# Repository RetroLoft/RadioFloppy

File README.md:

# RadioFloppy

WiFi-floppy-emulator voor de Atari ST op basis van een ESP32-S3 (Otronic DevKitC-clone,
16 MB flash, 8 MB PSRAM) op de RadioFloppy-PCB revisie 2 (`hardware/v1.1`).
Framework: ESP-IDF v5.5.5 (C).

## Hardwaretests

`main/main.c` kiest welke test draait (roep de gewenste functie uit `main/tests.h` aan):

| Test | Bestand | Wat |
| ---- | ------- | --- |
| `floppy_emu_run()` (actief) | `main/floppy_app.c`, `sd_card.c`, `disk_copy.c`, `drive_emu.c`, `flux_stream.c`, `mfm_track.c`, `disk_image.c` | Floppy-emulatie als drive B: (`EMU_SELECT_LINE`). De image (.ST of HFE) komt van de SD-kaart (J5), bij opstarten zonder kaart uit de kopie van de laatste disk op de externe SPI-flash U2 (zie `docs/FLASH_LAYOUT.md`), of uit een tijdelijke PSRAM-upload (.ST). Alle 168 sporen worden bij het opstarten naar MFM gecodeerd in PSRAM (FlashFloppy-layout voor .ST: geen IAM, GAP4a 80, GAP2 22, GAP3 84). RMT+DMA speelt de fluxstroom op GPIO41 (0,8 us pulsen, 10 MHz), een tweede RMT-kanaal de INDEX-puls op GPIO1 (3 ms per 200 ms, synchroon gestart). WPROT volgt de schrijfbeveiliging van de disk; geschreven sectoren worden opgeslagen (zie `docs/API.md` → *Writing*). |
| (oud) `legacy/input_monitor.c` | niet gebouwd | Selectiebewuste monitor met TRACK0 uit de vorige fase, ter referentie. |
| `loopback_test_run()` | `main/loopback_test.c` | Zoekt continu welke Shugart-uitgang (ULN2003A) via een jumper op J1 met welke ingang (SN74LVC245A) verbonden is. |

**Loopbacktest:** de Shugart-lijnen hebben op de PCB geen pull-ups (behalve DS0/DS1). Plaats op de jumper een
pull-up van 4,7–10 kΩ naar +3V3 (bijv. J3 pin 3, displayconnector), anders komt de lijn na het
vrijgeven van de uitgang niet betrouwbaar HIGH en wordt er niets gemeld.

**Webinterface:** `http://<ip>/` — Current Floppy, tijdelijk laden (PSRAM), *New disk* en het SD-kaartblok (mappen, uploaden, inserten, verwijderen) vanuit de browser
(`web/index.html`, in de firmware ingebouwd); tandwiel rechtsboven = instellingen (hostnaam,
firmware). **Knoppen:** links = vorige disk, rechts = volgende, binnen de map van de laatst gekozen disk (geen rondgang); beide 3 s = hostnaam en IP op het
display; beide 10 s = WiFi-setupmodus.

**WiFi-setupmodus:** zonder ingesteld netwerk (of na 10 s beide knoppen) opent RadioFloppy een
eigen WiFi-netwerk met één setup-pagina (netwerk, beveiliging, wachtwoord). De diskemulatie is dan
uit; het display toont netwerknaam, sleutel en adres. Zie `docs/API.md` → *WiFi setup mode*.

**WiFi en HTTP API:** `docs/API.md` — images uploaden (tijdelijk naar PSRAM of als bestand op de SD-kaart),
images van de SD-kaart inserten, mappen en bestanden beheren via `/api/v1/`. Hostnaam en WiFi-netwerk staan op de
externe flash (instellingen, setupmodus); `idf.py menuconfig` → *RadioFloppy* geeft alleen de
standaardwaarden en het optionele API-token, en staat alleen in `sdkconfig` (git-ignored). Standaard is de
API open op het thuisnetwerk. Tests:
`tests/host/run.sh` (op de PC), `tests/api/api_test.py` en `tests/web/ui_test.py` (tegen het board).

**STEP-geluid en LED's:** bij iedere verwerkte STEP-puls van drive B: geeft de buzzer (GPIO46) een tik van 3 ms (`main/step_sound.h`). De LED's (`main/leds.h`, instelling *Front panel LEDs*: 1 of 2): de LED op J4 pin 3 (GPIO20) brandt zolang drive B: geselecteerd is en MOTOR actief is. De WiFi-status staat met 2 LED's op J4 pin 1 (GPIO48), met 1 LED op de RGB-LED van het ESP32-bord (blauw): uit = verbonden, knippert = verbinding zoeken, brandt = na 60 s nog geen verbinding (of geen netwerk ingesteld), snel knipperen = WiFi-setupmodus.

**Buzzer:** hangt aan het +5V-net van de PCB, dat alleen via J2 (floppyvoeding / Atari) gevoed
wordt: de 5V-pin van de Otronic-clone is alleen een ingang. Bij voeding via USB alleen is de
buzzer dus stil.

**Veiligheid Shugart-uitgangen:** `bootloader_components/early_pins` zet de zes uitgangs-GPIO's
(ULN2003A-ingangen) al in de bootloader op LOW; `shugart_outputs_release()` doet dat opnieuw als
eerste stap in `app_main()`.

**Floppy images:** de firmware bevat geen images. De images staan als bestanden op de SD-kaart,
onder de ingestelde root directory. De externe flash bevat alleen de instellingen en een kopie van
de laatste disk (`docs/FLASH_LAYOUT.md`), zodat RadioFloppy ook zonder kaart met die disk start.
De oude imagebibliotheek op de flash wordt bij de eerste start van deze firmware gewist. De Atari
kan schrijven naar .ST-bestanden zonder het FAT-kenmerk alleen-lezen (slotje op de website); een
save gaat eerst naar de kopie in de flash (journaal) en dan naar het bestand op de kaart. `images/RETROLOFT_TEST_720K.ST` is alleen een testbestand in de
repository. Commerciële images blijven lokaal (`.gitignore`).

Volledige pinmapping: `main/board_pins.h`.

## Welke USB-poort?

Gebruik **uitsluitend de USB-poort van de USB-naar-UART-brug** (op het board meestal
gemarkeerd als `COM` of `UART`). De andere poort (`USB`) is de native USB van de ESP32-S3 en
zit direct op GPIO19/GPIO20. Die poort mag **niet** worden aangesloten: de host trekt D-/D+
via 15 kΩ naar GND, waardoor de knop SW_NEXT (GPIO19) permanent "ingedrukt" leest.

Controle onder Linux na het insteken:

```sh
lsusb
ls -l /dev/ttyUSB* /dev/ttyACM*
```

| `lsusb` toont                         | Poort                          |
| ------------------------------------- | ------------------------------ |
| `10c4:ea60` Silicon Labs CP210x       | UART-brug → goed (`/dev/ttyUSB0`) |
| `1a86:55d3` / `1a86:7523` QinHeng CH343/CH340 | UART-brug → goed (`/dev/ttyACM0` of `/dev/ttyUSB0`) |
| `303a:1001` Espressif USB JTAG/serial | native USB → **verkeerde poort** |

## Compileren, flashen en monitor

```sh
. ~/esp/esp-idf/export.sh           # eenmalig per terminal
cd FloppyEmulator-ESP32S3
idf.py set-target esp32s3           # alleen de eerste keer
idf.py build
idf.py -p /dev/ttyUSB0 flash monitor
```

Vervang `/dev/ttyUSB0` door de poort die hierboven is gevonden. Stoppen van de monitor:
`Ctrl+]`.

Verwachte uitvoer: de opstartmelding van RadioFloppy met de imagebibliotheek, de actieve disk
en het IP-adres.

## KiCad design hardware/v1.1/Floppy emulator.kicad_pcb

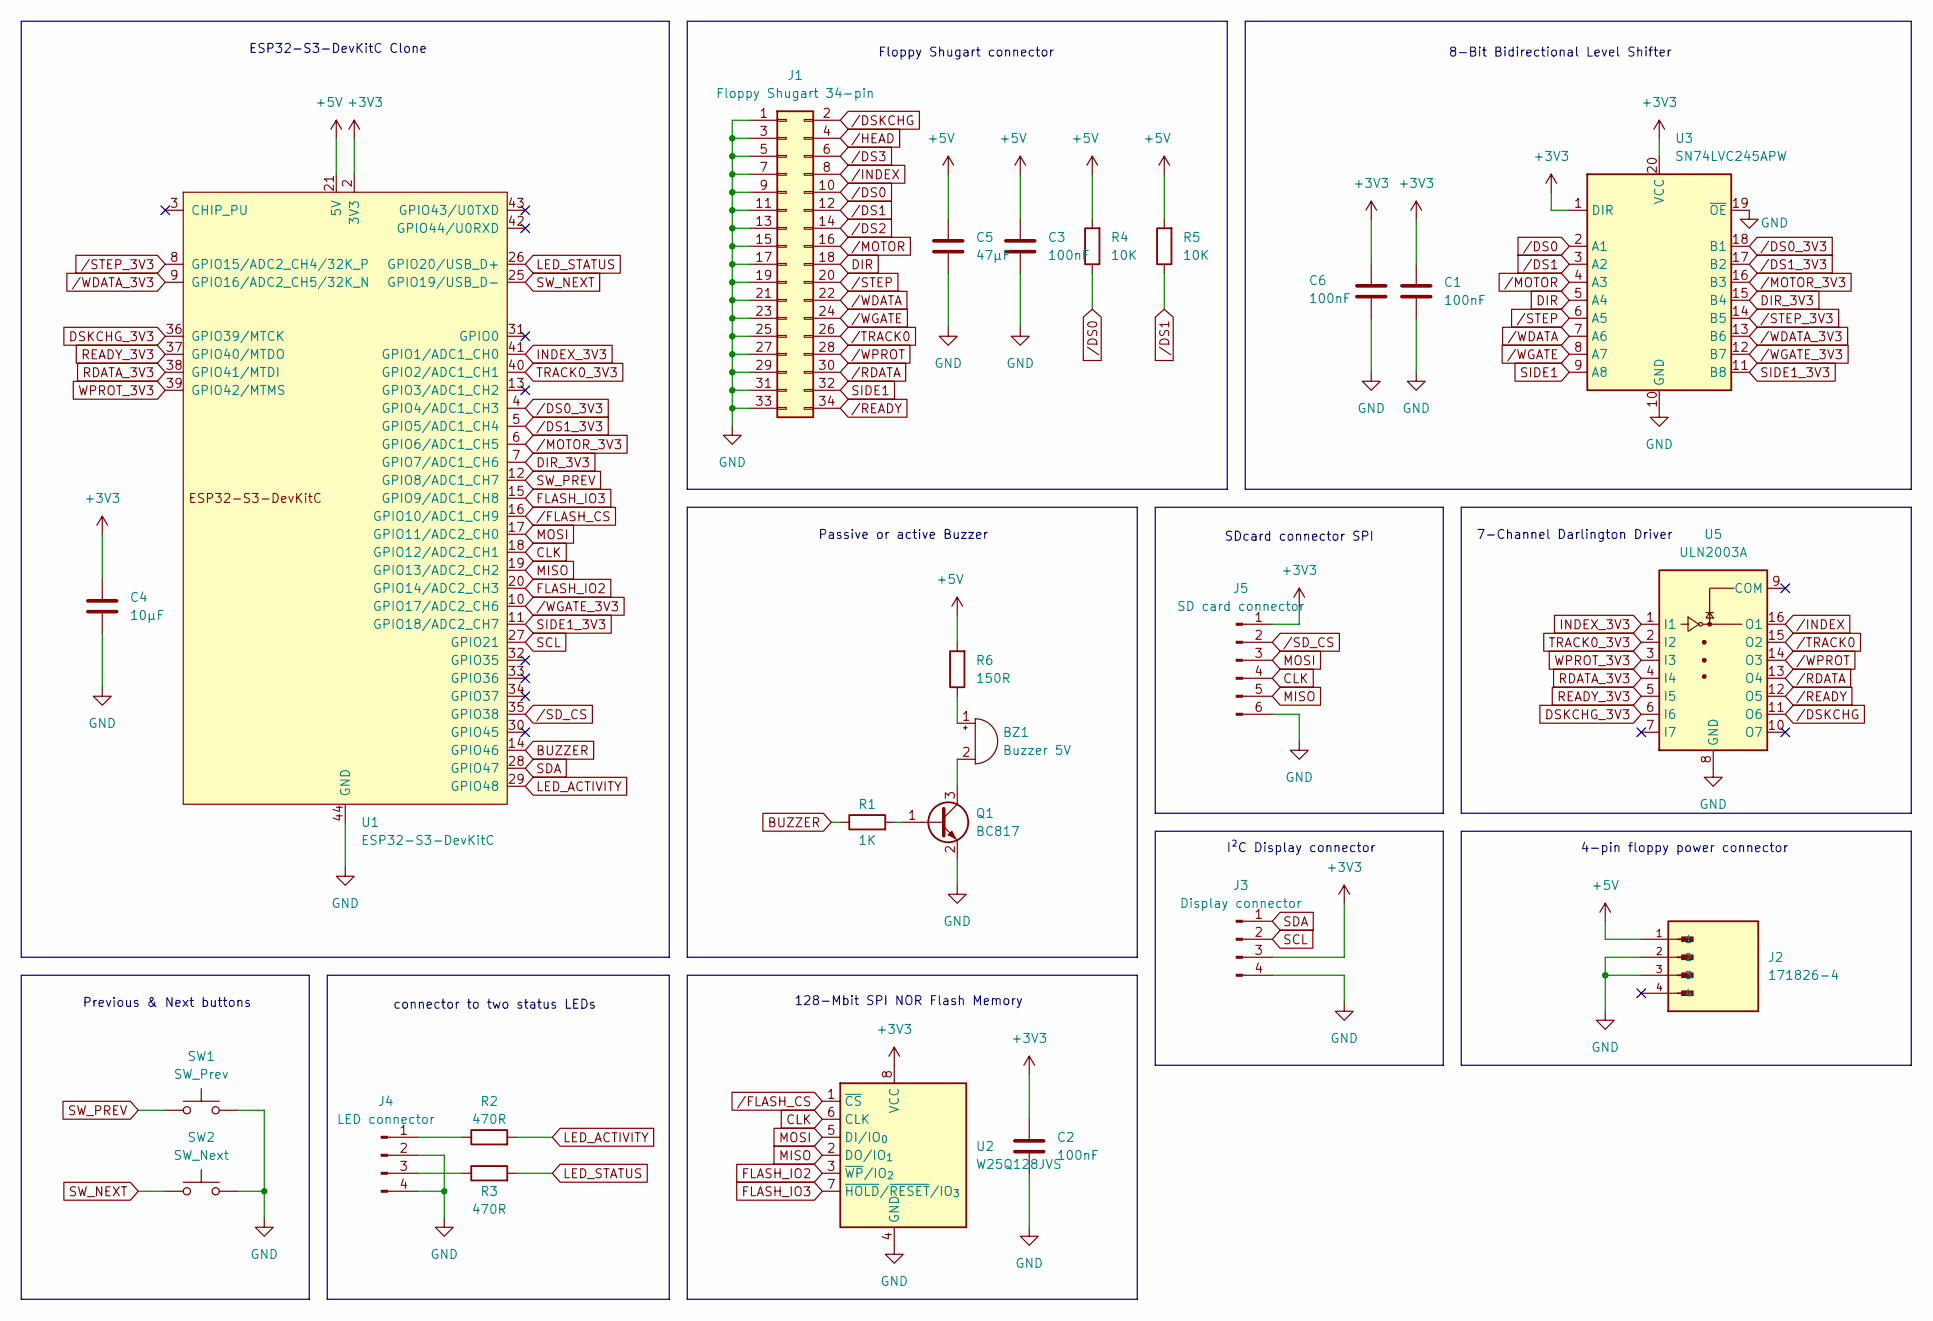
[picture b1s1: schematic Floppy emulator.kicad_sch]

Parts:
BZ1: Buzzer 5V; Buzzer_15x7.5RM7.6
C1, C2, C3, C6: 100nF; C_0805_2012Metric
C4: 10µF; C_0805_2012Metric
C5: 47µF; C_0805_2012Metric
J1: Floppy Shugart 34-pin; PinHeader_2x17_P2.54mm_Vertical
J2: 171826-4; TE_171826-4
J3: Display connector; PinHeader_1x04_P2.54mm_Vertical
J4: LED connector; PinHeader_1x04_P2.54mm_Vertical
J5: SD card connector; PinHeader_1x06_P2.54mm_Vertical
Q1: BC817; SOT-23
R1: 1K; R_0805_2012Metric
R2, R3: 470R; R_0805_2012Metric
R4, R5: 10K; R_0805_2012Metric
R6: 150R; R_0805_2012Metric
SW1: SW_Prev; SW_Tactile_SKHH_Angled
SW2: SW_Next; SW_Tactile_SKHH_Angled
U1: ESP32-S3-DevKitC; ESP32-S3-DevKitC-OTRONIC
U2: W25Q128JVS; SOIC-8_5.3x5.3mm_P1.27mm
U3: SN74LVC245APW; SOIC-20W_7.5x12.8mm_P1.27mm
U5: ULN2003A; SOIC-16_3.9x9.9mm_P1.27mm

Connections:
+3V3: C1.1, C2.1, C4.1, C6.1, J3.3, J5.1, U1.1 (3V3), U1.2 (3V3), U2.8 (VCC), U3.1 (DIR), U3.20 (VCC)
+5V: C3.1, C5.1, J2.1, R4.2, R5.2, R6.2, U1.21 (5V)
BUZZER: R1.1, U1.14 (GPIO46)
CLK: J5.4, U1.18 (GPIO12/ADC2_CH1), U2.6 (CLK)
DIR: J1.18, U3.5 (A4)
DIR_3V3: U1.7 (GPIO7/ADC1_CH6), U3.15 (B4)
DSKCHG_3V3: U1.36 (GPIO39/MTCK), U5.6 (I6)
FLASH_IO2: U1.20 (GPIO14/ADC2_CH3), U2.3 (~WP/IO_{2})
FLASH_IO3: U1.15 (GPIO9/ADC1_CH8), U2.7 (~HOLD/~RESET/IO_{3})
GND: C1.2, C2.2, C3.2, C4.2, C5.2, C6.2, J1.1, J1.3, J1.5, J1.7, J1.9, J1.11, J1.13, J1.15, J1.17, J1.19, J1.21, J1.23, J1.25, J1.27, J1.29, J1.31, J1.33, J2.2, J2.3, J3.4, J4.2, J4.4, J5.6, Q1.2 (E), SW1.2, SW2.2, U1.22 (GND), U1.23 (GND), U1.24 (GND), U1.44 (GND), U2.4 (GND), U3.10 (GND), U3.19 (~OE), U5.8 (GND)
INDEX_3V3: U1.41 (GPIO1/ADC1_CH0), U5.1 (I1)
LED_ACTIVITY: R2.2, U1.29 (GPIO48)
LED_STATUS: R3.2, U1.26 (GPIO20/USB_D+)
MISO: J5.5, U1.19 (GPIO13/ADC2_CH2), U2.2 (DO/IO_{1})
MOSI: J5.3, U1.17 (GPIO11/ADC2_CH0), U2.5 (DI/IO_{0})
unnamed: BZ1.1 (+), R6.1
unnamed: BZ1.2 (-), Q1.3 (C)
unnamed: J4.1, R2.1
unnamed: J4.3, R3.1
unnamed: Q1.1 (B), R1.2
RDATA_3V3: U1.38 (GPIO41/MTDI), U5.4 (I4)
READY_3V3: U1.37 (GPIO40/MTDO), U5.5 (I5)
SCL: J3.2, U1.27 (GPIO21)
SDA: J3.1, U1.28 (GPIO47)
SIDE1: J1.32, U3.9 (A8)
SIDE1_3V3: U1.11 (GPIO18/ADC2_CH7), U3.11 (B8)
SW_NEXT: SW2.1, U1.25 (GPIO19/USB_D-)
SW_PREV: SW1.1, U1.12 (GPIO8/ADC1_CH7)
TRACK0_3V3: U1.40 (GPIO2/ADC1_CH1), U5.2 (I2)
WPROT_3V3: U1.39 (GPIO42/MTMS), U5.3 (I3)
/DS0: J1.10, R4.1, U3.2 (A1)
/DS0_3V3: U1.4 (GPIO4/ADC1_CH3), U3.18 (B1)
/DS1: J1.12, R5.1, U3.3 (A2)
/DS1_3V3: U1.5 (GPIO5/ADC1_CH4), U3.17 (B2)
/DS2: J1.14
/DS3: J1.6
/DSKCHG: J1.2, U5.11 (O6)
/FLASH_CS: U1.16 (GPIO10/ADC1_CH9), U2.1 (~CS)
/HEAD: J1.4
/INDEX: J1.8, U5.16 (O1)
/MOTOR: J1.16, U3.4 (A3)
/MOTOR_3V3: U1.6 (GPIO6/ADC1_CH5), U3.16 (B3)
/RDATA: J1.30, U5.13 (O4)
/READY: J1.34, U5.12 (O5)
/SD_CS: J5.2, U1.35 (GPIO38)
/STEP: J1.20, U3.6 (A5)
/STEP_3V3: U1.8 (GPIO15/ADC2_CH4/32K_P), U3.14 (B5)
/TRACK0: J1.26, U5.15 (O2)
/WDATA: J1.22, U3.7 (A6)
/WDATA_3V3: U1.9 (GPIO16/ADC2_CH5/32K_N), U3.13 (B6)
/WGATE: J1.24, U3.8 (A7)
/WGATE_3V3: U1.10 (GPIO17/ADC2_CH6), U3.12 (B7)
/WPROT: J1.28, U5.14 (O3)

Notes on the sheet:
Previous & Next buttons
8-Bit Bidirectional Level Shifter
Passive or active Buzzer
connector to two status LEDs
SDcard connector SPI
I²C Display connector
Floppy Shugart connector
7-Channel Darlington Driver
4-pin floppy power connector
ESP32-S3-DevKitC Clone
128-Mbit SPI NOR Flash Memory

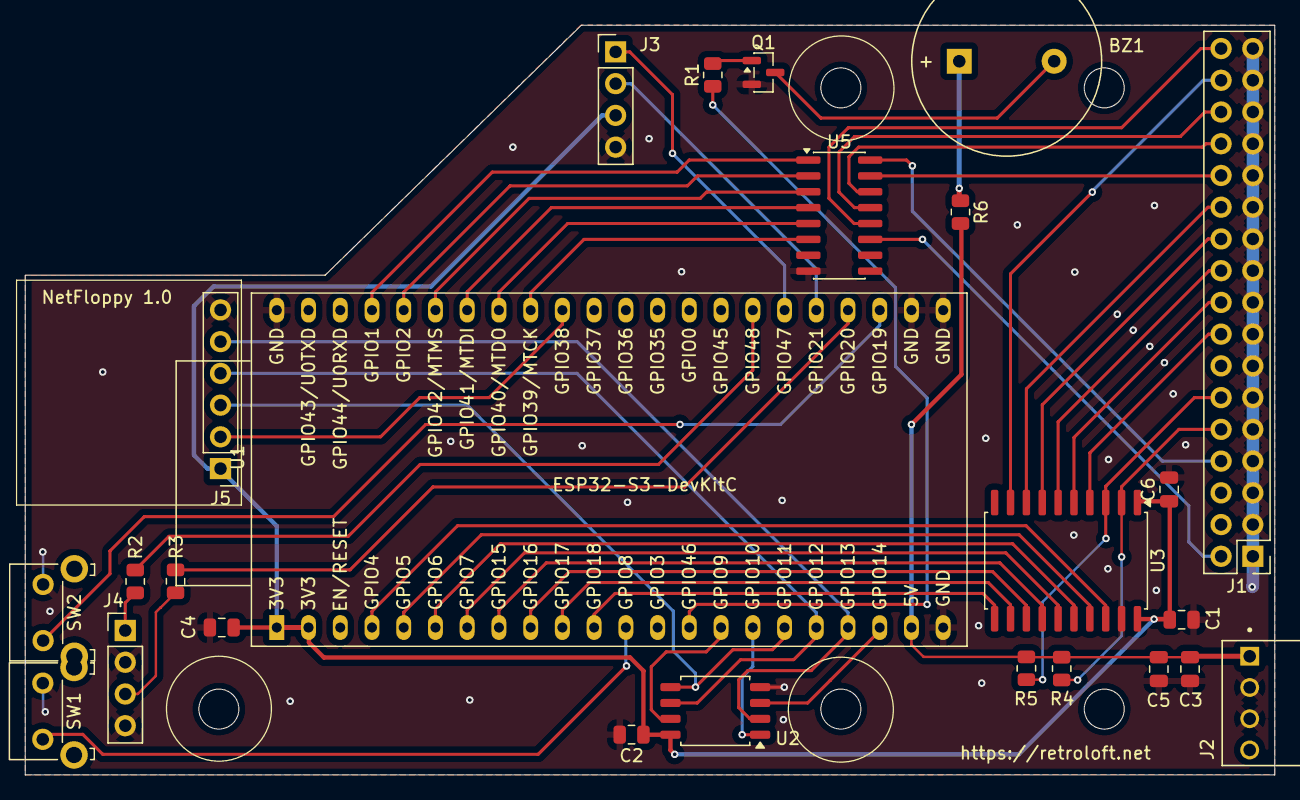
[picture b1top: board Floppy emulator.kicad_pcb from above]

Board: 2 copper layers, 100.0 x 60.0 mm, 25 parts (0 on the bottom side), 50 nets.

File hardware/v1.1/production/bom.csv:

Designator,Footprint,Quantity,Value,LCSC Part #
BZ1,Buzzer_15x7.5RM7.6,1,Active buzzer 5V,
"C1, C2, C3, C6",0805,4,100nF,
C4,0805,1,10µF,
C5,0805,1,47µF,
J1,PinHeader_2x17_P2.54mm_Vertical,1,Floppy Shugart 34-pin,
J2,TE_171826-4,1,171826-4,
J3,PinHeader_1x04_P2.54mm_Vertical,1,Display connector,
J4,PinHeader_1x04_P2.54mm_Vertical,1,LED connector,
J5,PinHeader_1x06_P2.54mm_Vertical,1,Conn_01x06_Pin,
Q1,SOT-23,1,BC817,
R1,0805,1,1K,
"R2, R3",0805,2,470R,
"R4, R5",0805,2,10K,
R6,0805,1,150R,
SW1,SW_Tactile_SKHH_Angled,1,SW_Prev,
SW2,SW_Tactile_SKHH_Angled,1,SW_Next,
U1,ESP32-S3-DevKitC-OTRONIC,1,ESP32-S3-DevKitC,
U2,SOIC-8_5.3x5.3mm_P1.27mm,1,W25Q128JVS,
U3,SOIC-20W_7.5x12.8mm_P1.27mm,1,SN74LVC245APW,
U5,SOIC-16_3.9x9.9mm_P1.27mm,1,ULN2003A,

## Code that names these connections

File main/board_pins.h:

/*
 * Pin mapping of the RadioFloppy PCB, revision 2 (hardware/v1.1):
 * ESP32-S3-DevKitC (Otronic, N16R8) on the carrier board.
 *
 * Source: hardware/v1.1/"Floppy emulator.kicad_pcb" (U1 footprint pads and
 * their nets), checked against the user's hardware description on
 * 2026-09-29. All pins match.
 */
#pragma once

#include "driver/gpio.h"

/* Push buttons: switch to GND, use internal pull-up, active low.
 * On revision 1 SW_PREV was physically the RIGHT button and SW_NEXT the
 * LEFT one; check this again on the revision 2 board. */
#define PIN_BTN_PREV        GPIO_NUM_8   /* SW1 / SW_PREV - right */
#define PIN_BTN_NEXT        GPIO_NUM_19  /* SW2 / SW_NEXT - left (also native USB D-) */

/* Console: UART0 via the DevKitC USB-to-UART bridge. */
#define PIN_UART0_TX        GPIO_NUM_43
#define PIN_UART0_RX        GPIO_NUM_44

/* Shugart inputs (Atari -> ESP32) through SN74LVC245A, active low.
 * DS0/DS1 have 10k pull-ups to +5 V on the connector side (R4/R5); the
 * other inputs float while the computer is off. */
#define PIN_FDD_DS0         GPIO_NUM_4
#define PIN_FDD_DS1         GPIO_NUM_5
#define PIN_FDD_MOTOR       GPIO_NUM_6
#define PIN_FDD_DIR         GPIO_NUM_7
#define PIN_FDD_STEP        GPIO_NUM_15
#define PIN_FDD_WDATA       GPIO_NUM_16
#define PIN_FDD_WGATE       GPIO_NUM_17
#define PIN_FDD_SIDE        GPIO_NUM_18

/* Shugart outputs (ESP32 -> Atari) through ULN2003A (open collector):
 * GPIO HIGH = line pulled LOW on the connector = signal asserted. */
#define PIN_FDD_INDEX       GPIO_NUM_1
#define PIN_FDD_TRK0        GPIO_NUM_2
#define PIN_FDD_WPROT       GPIO_NUM_42
#define PIN_FDD_RDATA       GPIO_NUM_41
#define PIN_FDD_READY       GPIO_NUM_40
#define PIN_FDD_DSKCHG      GPIO_NUM_39

/* One SPI bus (SPI2) for the NOR flash (U2) and the external SD card
 * module (J5). Each has its own CS; both CS lines must be HIGH whenever
 * the other device is used. */
#define PIN_SPI_MOSI        GPIO_NUM_11
#define PIN_SPI_CLK         GPIO_NUM_12
#define PIN_SPI_MISO        GPIO_NUM_13

/* External SPI NOR flash (schematic: W25Q128JVS; the fitted part on the
 * first boards is an S25FL128L). */
#define PIN_NOR_CS          GPIO_NUM_10
#define PIN_NOR_MOSI        PIN_SPI_MOSI  /* IO0 */
#define PIN_NOR_CLK         PIN_SPI_CLK
#define PIN_NOR_MISO        PIN_SPI_MISO  /* IO1 */
#define PIN_NOR_WP          GPIO_NUM_14   /* IO2 */
#define PIN_NOR_HOLD        GPIO_NUM_9    /* IO3 */

/* External SD card module (J5), SPI mode. */
#define PIN_SD_CS           GPIO_NUM_38

/* I2C display (J3). */
#define PIN_I2C_SDA         GPIO_NUM_47
#define PIN_I2C_SCL         GPIO_NUM_21

/* Active 5 V buzzer via BC817 (1k to the base). GPIO46 is a strapping
 * pin: pulled low at reset, so the buzzer is silent while booting. */
#define PIN_BUZZER          GPIO_NUM_46

/* LEDs on J4, each through 470R, active high (PCB nets LED_ACTIVITY and
 * LED_STATUS; what they show depends on the "leds" setting, see leds.h).
 * GPIO48 also drives the DevKitC's on-board RGB LED data input.
 * GPIO20 is the native USB D+ pad (see board.c). */
#define PIN_LED_J4_PIN1     GPIO_NUM_48
#define PIN_LED_J4_PIN3     GPIO_NUM_20

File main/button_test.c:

/*
 * FloppyEmulator-ESP32S3 - push button + buzzer test.
 *
 * Prints a message on the UART0 console for every press of the left
 * (SW_NEXT, GPIO19) or right (SW_PREV, GPIO8) button. Buttons pull the
 * GPIO to GND; internal pull-ups are used. Software debounce: a new level
 * is only accepted after it has been stable for DEBOUNCE_MS.
 *
 * Phase 2: the active 5 V buzzer (GPIO20 -> BC817 low-side switch,
 * HIGH = on) beeps once for BEEP_STARTUP_MS after start-up.
 */
#include <stdio.h>
#include <stdbool.h>

#include "freertos/FreeRTOS.h"
#include "freertos/task.h"
#include "driver/gpio.h"

#include "board_pins.h"
#include "tests.h"

#define POLL_INTERVAL_MS    5
#define DEBOUNCE_MS         30
#define BEEP_STARTUP_MS     500

typedef struct {
    gpio_num_t pin;
    const char *name;
    int stable_level;       /* debounced level */
    int last_raw_level;     /* level seen at previous poll */
    TickType_t changed_at;  /* tick of the last raw level change */
} button_t;

static button_t buttons[] = {
    { .pin = PIN_BTN_NEXT, .name = "Left Button"  },
    { .pin = PIN_BTN_PREV, .name = "Right Button" },
};

#define NUM_BUTTONS (sizeof(buttons) / sizeof(buttons[0]))

static void buzzer_init(void)
{
    const gpio_config_t cfg = {
        .pin_bit_mask = 1ULL << PIN_BUZZER,
        .mode = GPIO_MODE_OUTPUT,
        .pull_up_en = GPIO_PULLUP_DISABLE,
        .pull_down_en = GPIO_PULLDOWN_DISABLE,
        .intr_type = GPIO_INTR_DISABLE,
    };
    /* Set the output latch low before enabling the driver so the buzzer
     * stays silent. For GPIO20 this also detaches the native USB D+ pad. */
    gpio_set_level(PIN_BUZZER, 0);
    ESP_ERROR_CHECK(gpio_config(&cfg));
}

static void buzzer_beep(uint32_t duration_ms)
{
    gpio_set_level(PIN_BUZZER, 1);
    vTaskDelay(pdMS_TO_TICKS(duration_ms));
    gpio_set_level(PIN_BUZZER, 0);
}

static void buttons_init(void)
{
    const gpio_config_t cfg = {
        .pin_bit_mask = (1ULL << PIN_BTN_PREV) | (1ULL << PIN_BTN_NEXT),
        .mode = GPIO_MODE_INPUT,
        .pull_up_en = GPIO_PULLUP_ENABLE,
        .pull_down_en = GPIO_PULLDOWN_DISABLE,
        .intr_type = GPIO_INTR_DISABLE,
    };
    /* For GPIO19 this also detaches the pad from the native USB PHY. */
    ESP_ERROR_CHECK(gpio_config(&cfg));

    /* Let the pull-ups settle, then take the current level as the start
     * state so a button held during reset does not produce a message. */
    vTaskDelay(pdMS_TO_TICKS(10));
    TickType_t now = xTaskGetTickCount();
    for (size_t i = 0; i < NUM_BUTTONS; i++) {
        int level = gpio_get_level(buttons[i].pin);
        buttons[i].stable_level = level;
        buttons[i].last_raw_level = level;
        buttons[i].changed_at = now;
    }
}

static void buttons_poll(void)
{
    TickType_t now = xTaskGetTickCount();

    for (size_t i = 0; i < NUM_BUTTONS; i++) {
        button_t *b = &buttons[i];
        int raw = gpio_get_level(b->pin);

        if (raw != b->last_raw_level) {
            b->last_raw_level = raw;
            b->changed_at = now;
        } else if (raw != b->stable_level &&
                   (now - b->changed_at) >= pdMS_TO_TICKS(DEBOUNCE_MS)) {
            b->stable_level = raw;
            if (raw == 0) {          /* active low: 0 = pressed */
                printf("%s\n", b->name);
            }
        }
    }
}

void button_test_run(void)
{
    printf("\nFloppy Emulator - Button Test\n");

    buzzer_init();
    buttons_init();

    printf("Ready. Press a button.\n");

    buzzer_beep(BEEP_STARTUP_MS);

    while (true) {
        buttons_poll();
        vTaskDelay(pdMS_TO_TICKS(POLL_INTERVAL_MS));
    }
}
